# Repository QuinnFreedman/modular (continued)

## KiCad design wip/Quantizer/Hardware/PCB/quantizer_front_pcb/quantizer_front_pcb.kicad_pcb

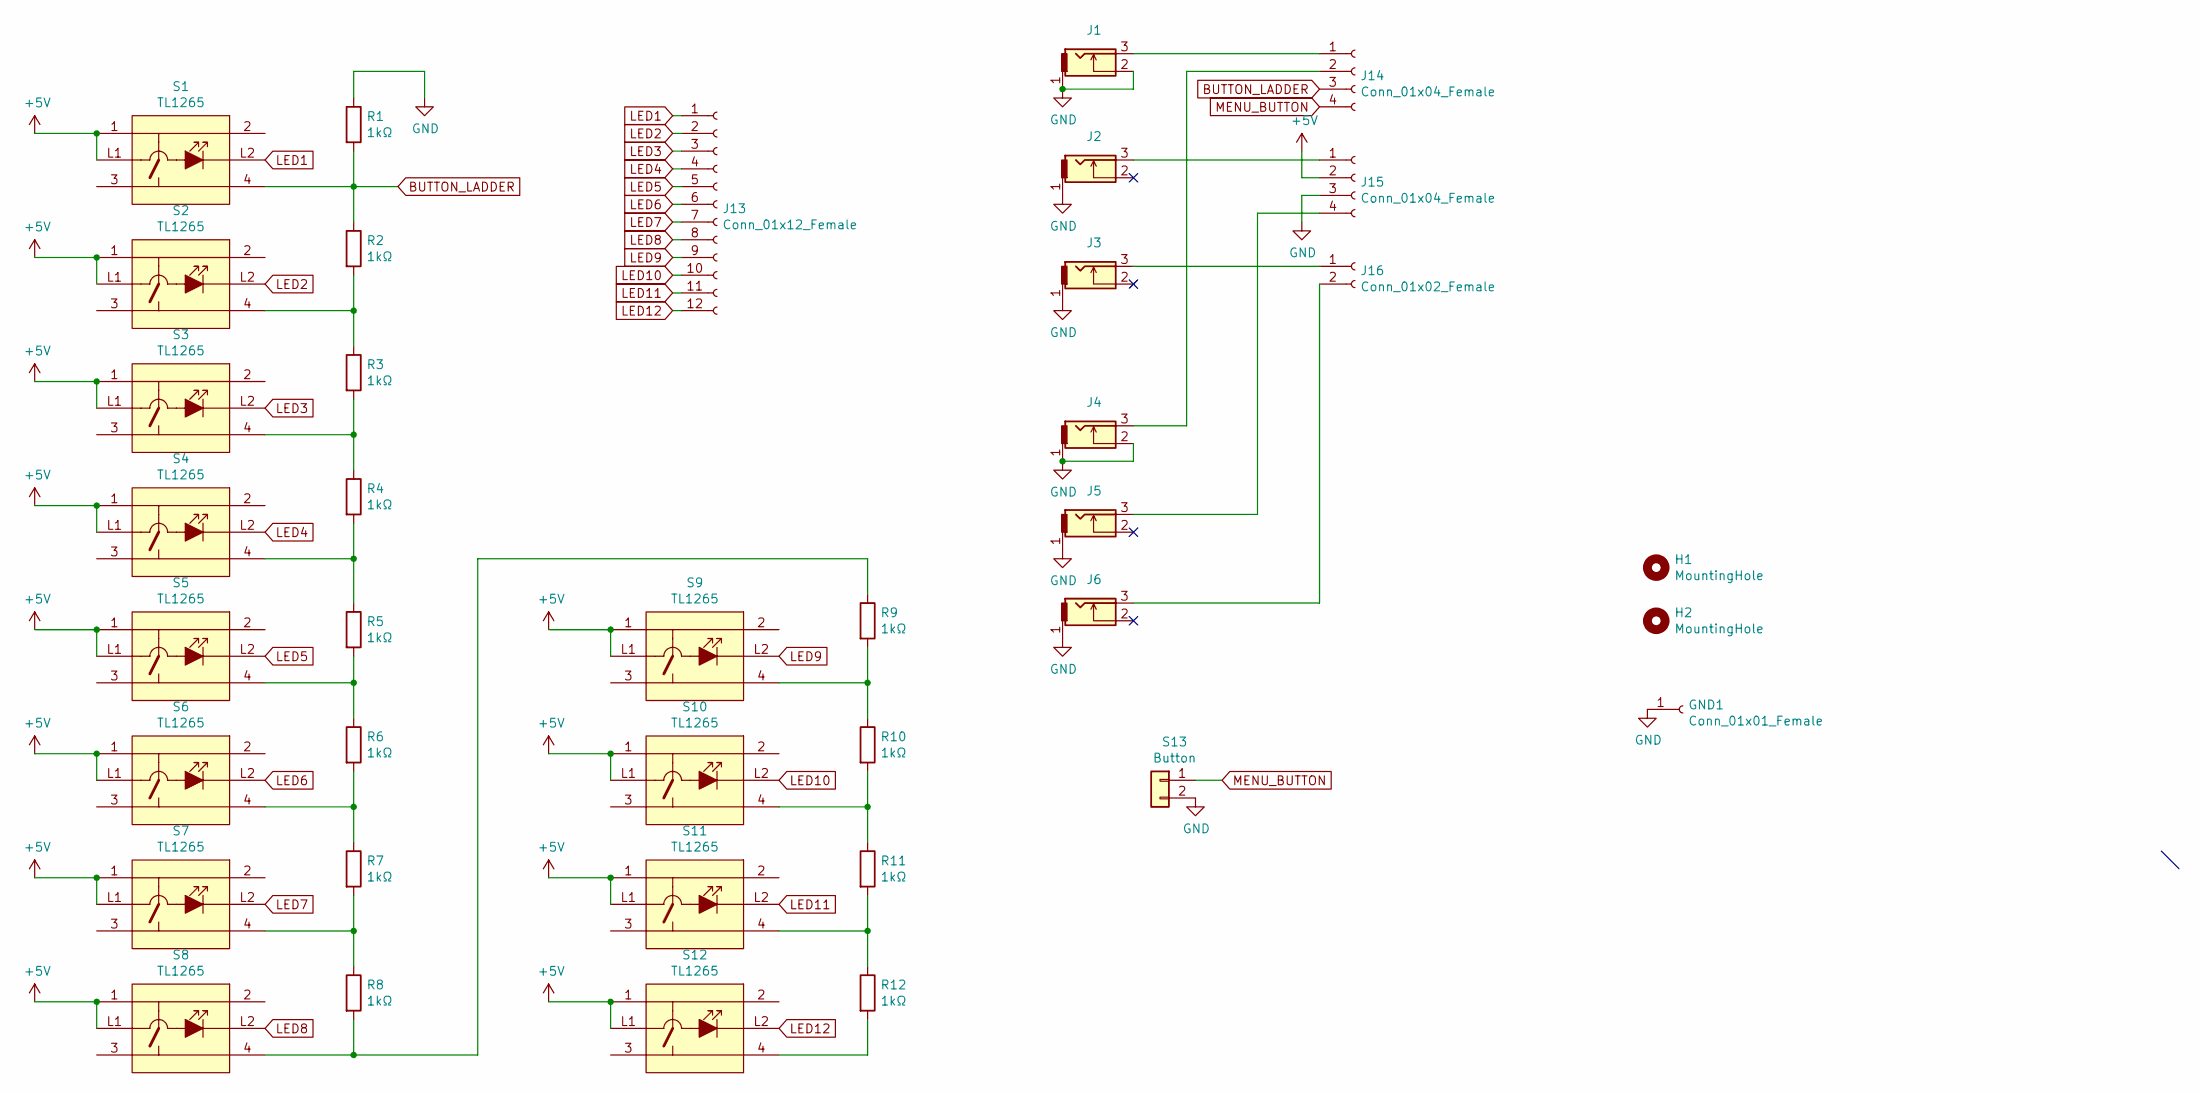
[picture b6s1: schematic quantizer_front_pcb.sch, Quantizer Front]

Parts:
GND1: Conn_01x01_Female; SolderWire-0.5sqmm_1x01_D0.9mm_OD2.1mm
H1, H2: MountingHole; MountingHole_2.7mm_M2.5
J1, J2, J3, J4, J5, J6: THONKICONN
J13: Conn_01x12_Female; PinSocket_1x12_P2.54mm_Vertical
J14, J15: Conn_01x04_Female; PinSocket_1x04_P2.54mm_Vertical
J16: Conn_01x02_Female; PinSocket_1x02_P2.54mm_Vertical
R1, R2, R3, R4, R5, R6, R7, R8, R9, R10, R11, R12: 1kΩ; R_Axial_DIN0207_L6.3mm_D2.5mm_P10.16mm_Horizontal
S1, S2, S3, S4, S5, S6, S7, S8, S9, S10, S11, S12: TL1265; Mouser Part Number 612-TL1265BQSCLR
S13: Button; PinSocket_1x02_P2.54mm_Vertical

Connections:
+5V: J15.2, S1.1, S1.L1, S2.1, S2.L1, S3.1, S3.L1, S4.1, S4.L1, S5.1, S5.L1, S6.1, S6.L1, S7.1, S7.L1, S8.1, S8.L1, S9.1, S9.L1, S10.1, S10.L1, S11.1, S11.L1, S12.1, S12.L1
BUTTON_LADDER: J14.3, R1.2, R2.1, S1.4
GND: GND1.1, J1.1, J1.2, J2.1, J3.1, J4.1, J4.2, J5.1, J6.1, J15.3, R1.1, S13.2
LED1: J13.1, S1.L2
LED2: J13.2, S2.L2
LED3: J13.3, S3.L2
LED4: J13.4, S4.L2
LED5: J13.5, S5.L2
LED6: J13.6, S6.L2
LED7: J13.7, S7.L2
LED8: J13.8, S8.L2
LED9: J13.9, S9.L2
LED10: J13.10, S10.L2
LED11: J13.11, S11.L2
LED12: J13.12, S12.L2
MENU_BUTTON: J14.4, S13.1
unnamed: J1.3, J14.1
unnamed: J4.3, J14.2
unnamed: J2.3, J15.1
unnamed: J5.3, J15.4
unnamed: J3.3, J16.1
unnamed: J6.3, J16.2
unnamed: R2.2, R3.1, S2.4
unnamed: R3.2, R4.1, S3.4
unnamed: R4.2, R5.1, S4.4
unnamed: R5.2, R6.1, S5.4
unnamed: R6.2, R7.1, S6.4
unnamed: R7.2, R8.1, S7.4
unnamed: R8.2, R9.1, S8.4
unnamed: R9.2, R10.1, S9.4
unnamed: R10.2, R11.1, S10.4
unnamed: R11.2, R12.1, S11.4
unnamed: R12.2, S12.4

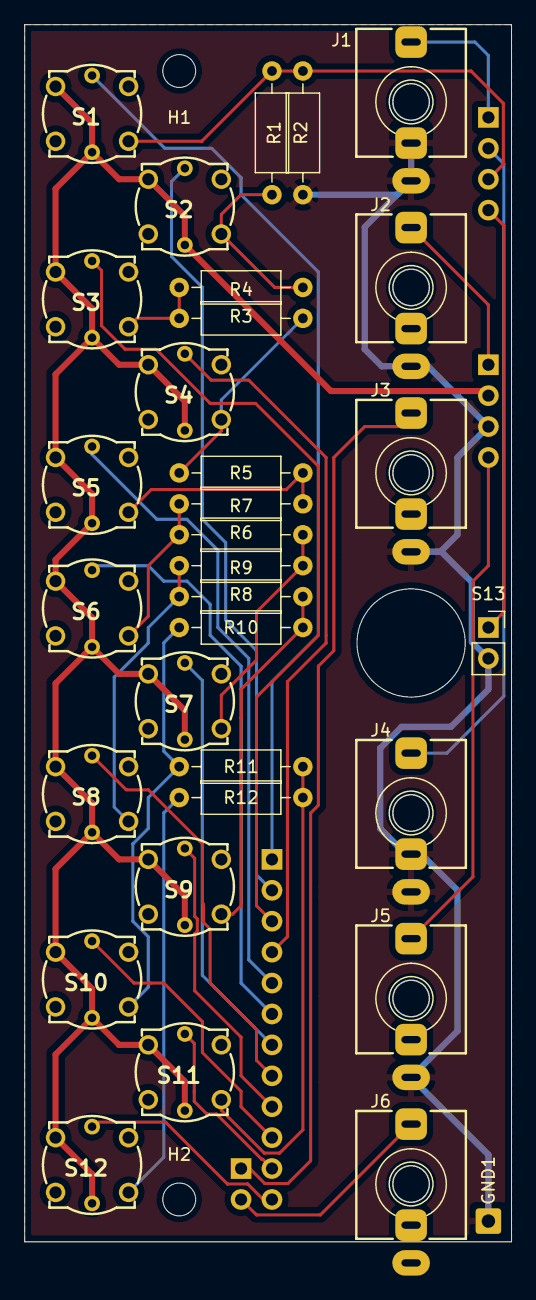
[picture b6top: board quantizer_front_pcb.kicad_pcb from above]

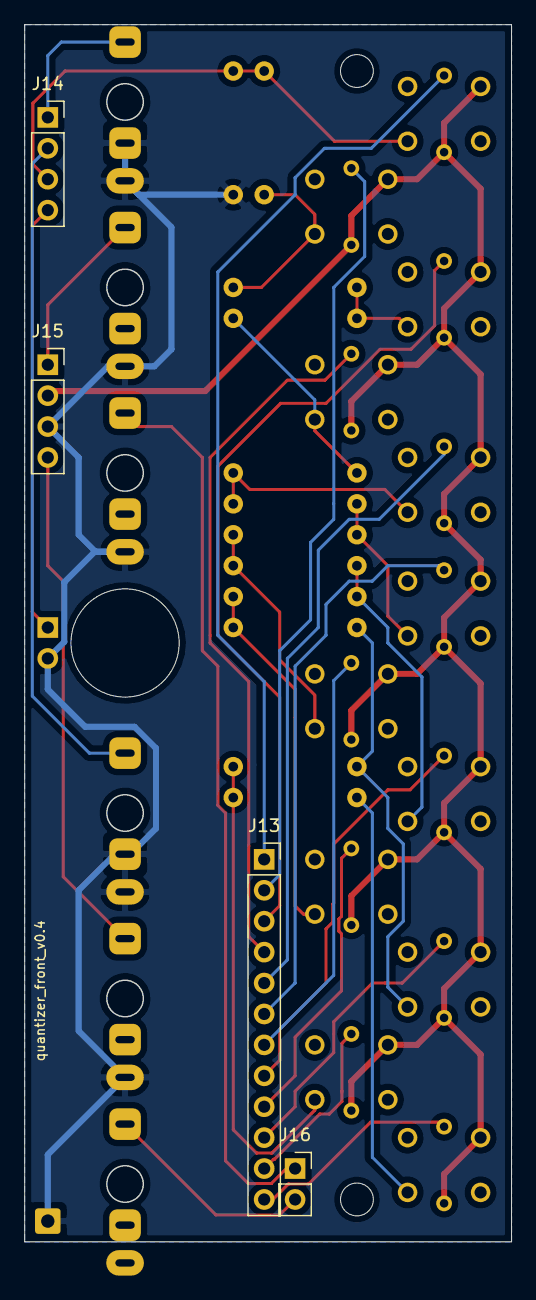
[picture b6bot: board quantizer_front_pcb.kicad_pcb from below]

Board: 2 copper layers, 40.0 x 100.0 mm, 38 parts (4 on the bottom side), 33 nets.
